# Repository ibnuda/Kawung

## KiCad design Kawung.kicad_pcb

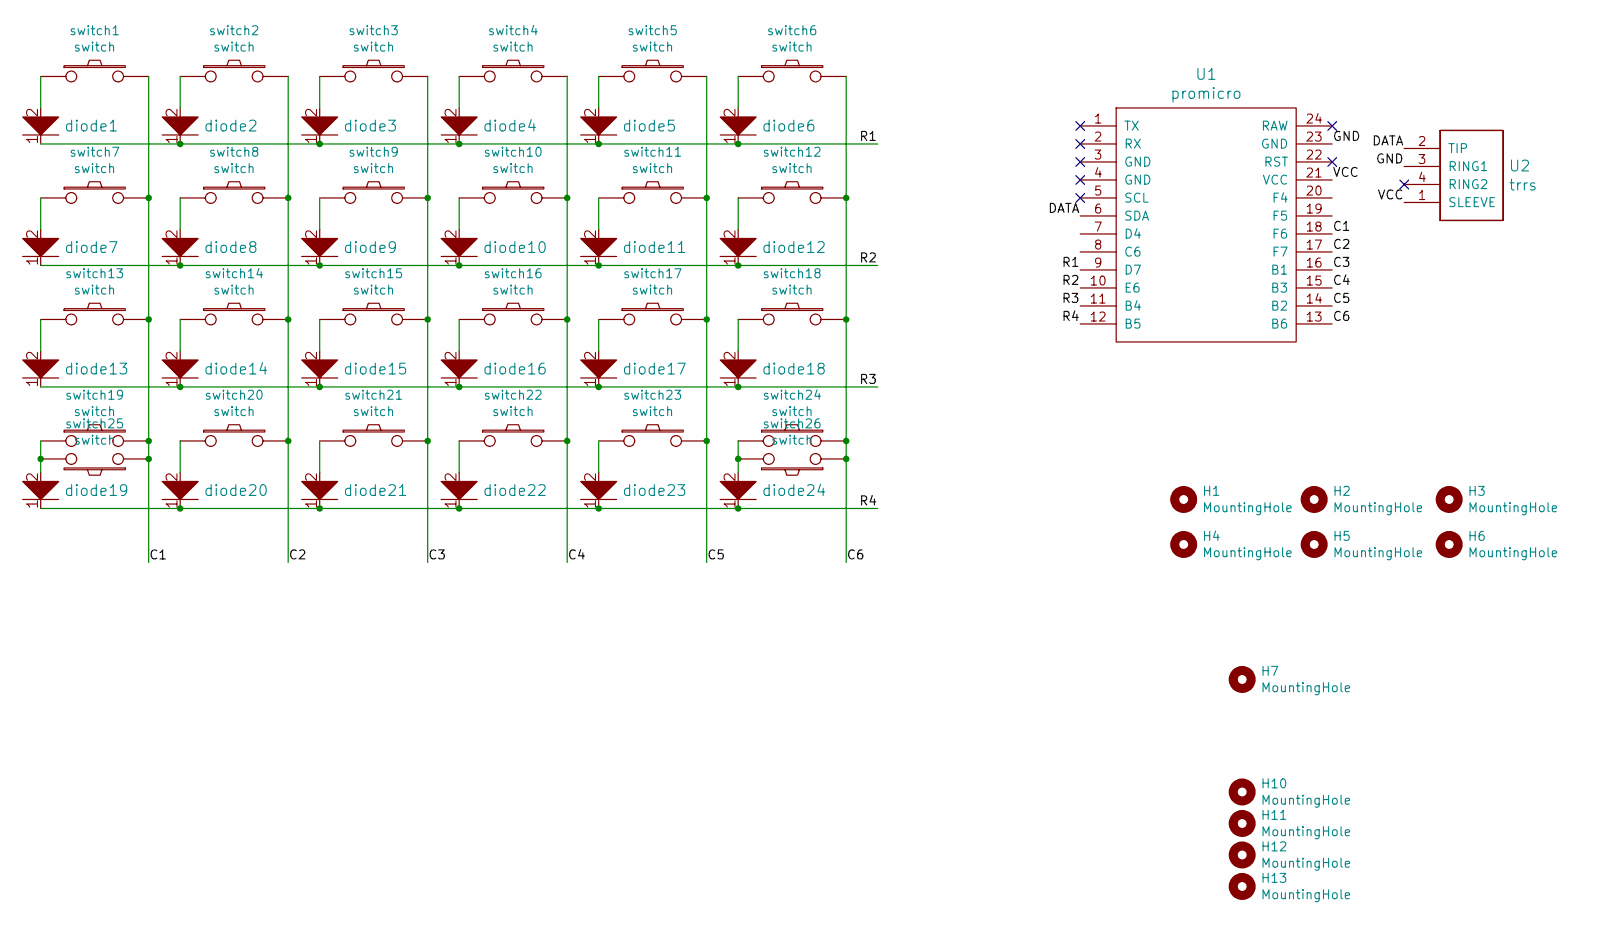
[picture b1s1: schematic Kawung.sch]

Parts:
H1, H2, H3, H4, H5, H6: MountingHole; hole-m2-pcb
H7: MountingHole; kawung_gedhe
H10, H11, H12, H13: MountingHole; kawung
U1: promicro
U2: trrs
diode1, diode2, diode3, diode4, diode5, diode6, diode7, diode8, diode9, diode10, diode11, diode12, diode13, diode14, diode15, diode16, diode17, diode18, diode19, diode20, diode21, diode22, diode23, diode24: diode
switch1, switch2, switch3, switch4, switch5, switch6, switch7, switch8, switch9, switch10, switch11, switch12, switch13, switch14, switch15, switch16, switch17, switch18, switch19, switch20, switch21, switch22, switch23, switch24: switch; 100-dual-no-3d
switch25, switch26: switch; 200-dual-no-3d

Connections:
/C1: U1.18 (F6), switch1.2, switch7.2, switch13.2, switch19.2, switch25.1
/C2: U1.17 (F7), switch2.2, switch8.2, switch14.2, switch20.2
/C3: U1.16 (B1), switch3.2, switch9.2, switch15.2, switch21.2
/C4: U1.15 (B3), switch4.2, switch10.2, switch16.2, switch22.2
/C5: U1.14 (B2), switch5.2, switch11.2, switch17.2, switch23.2
/C6: U1.13 (B6), switch6.2, switch12.2, switch18.2, switch24.2, switch26.1
/DATA: U1.6 (SDA), U2.2 (TIP)
/GND: U1.23 (GND), U2.3 (RING1)
/R1: U1.9 (D7), diode1.1, diode2.1, diode3.1, diode4.1, diode5.1, diode6.1
/R2: U1.10 (E6), diode7.1, diode8.1, diode9.1, diode10.1, diode11.1, diode12.1
/R3: U1.11 (B4), diode13.1, diode14.1, diode15.1, diode16.1, diode17.1, diode18.1
/R4: U1.12 (B5), diode19.1, diode20.1, diode21.1, diode22.1, diode23.1, diode24.1
/VCC: U1.21 (VCC), U2.1 (SLEEVE)
unnamed: diode1.2, switch1.1
unnamed: diode2.2, switch2.1
unnamed: diode3.2, switch3.1
unnamed: diode4.2, switch4.1
unnamed: diode5.2, switch5.1
unnamed: diode6.2, switch6.1
unnamed: diode7.2, switch7.1
unnamed: diode8.2, switch8.1
unnamed: diode9.2, switch9.1
unnamed: diode10.2, switch10.1
unnamed: diode11.2, switch11.1
unnamed: diode12.2, switch12.1
unnamed: diode13.2, switch13.1
unnamed: diode14.2, switch14.1
unnamed: diode15.2, switch15.1
unnamed: diode16.2, switch16.1
unnamed: diode17.2, switch17.1
unnamed: diode18.2, switch18.1
unnamed: diode19.2, switch19.1, switch25.2
unnamed: diode20.2, switch20.1
unnamed: diode21.2, switch21.1
unnamed: diode22.2, switch22.1
unnamed: diode23.2, switch23.1
unnamed: diode24.2, switch24.1, switch26.2

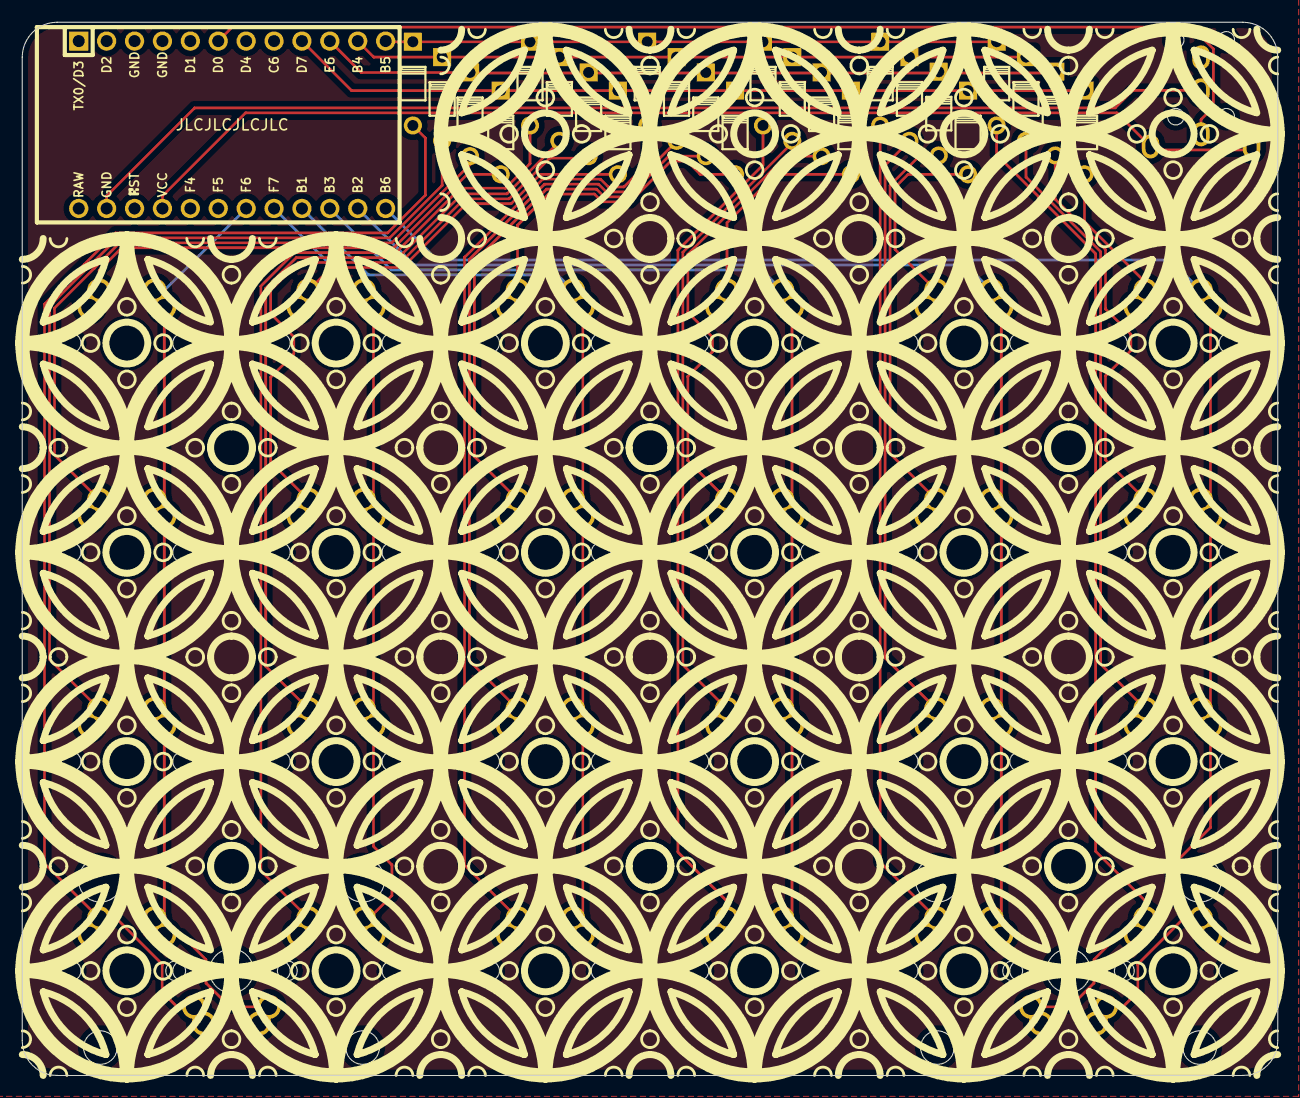
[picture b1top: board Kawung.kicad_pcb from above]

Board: 2 copper layers, 114.3 x 95.9 mm, 63 parts (1 on the bottom side), 37 nets.
